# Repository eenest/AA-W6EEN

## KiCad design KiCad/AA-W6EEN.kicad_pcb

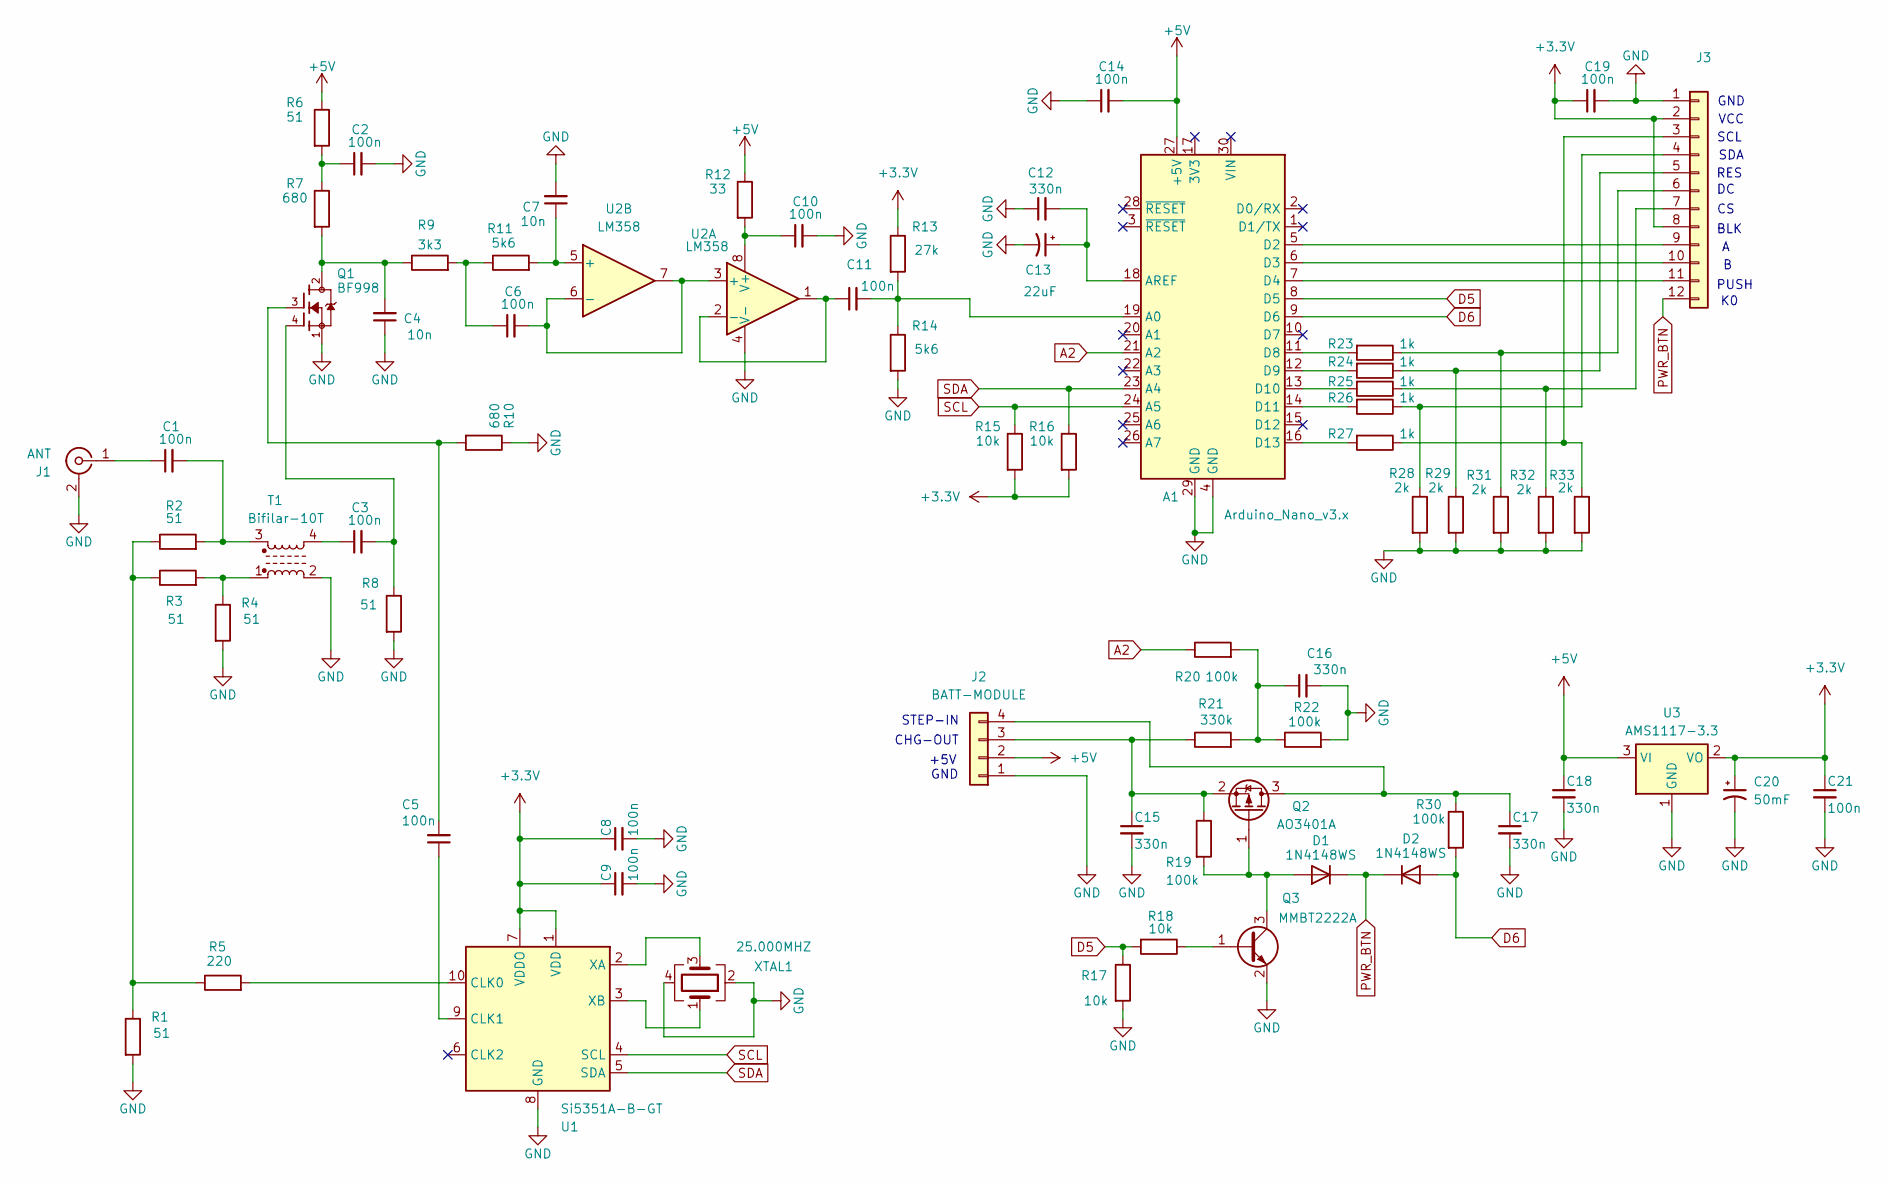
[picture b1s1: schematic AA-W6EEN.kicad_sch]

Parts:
A1: Arduino_Nano_v3.x; Arduino_Nano
C1, C2, C3, C5, C6, C8, C9, C10, C11, C14, C19, C21: 100n; C_0805_2012Metric_Pad1.18x1.45mm_HandSolder
C4, C7: 10n; C_0805_2012Metric_Pad1.18x1.45mm_HandSolder
C12, C15, C16, C17, C18: 330n; C_0805_2012Metric_Pad1.18x1.45mm_HandSolder
C13: 22uF; CP_Elec_4x3
C20: 50mF; C_Elec_6.3x7.7
D1, D2: 1N4148WS; D_SOD-123F
J1: ANT; BNC_Amphenol_B6252HB-NPP3G-50_Horizontal
J2: BATT-MODULE; JST_XH_B4B-XH-A_1x04_P2.50mm_Vertical
J3: 2.4" TFT with EC11; PinSocket_1x12_P2.54mm_Vertical
Q1: BF998; SOT190P230X110-4N
Q2: AO3401A; SOT-23
Q3: MMBT2222A; SOT-23
R1, R2, R3, R4, R6, R8: 51; R_0805_2012Metric_Pad1.20x1.40mm_HandSolder
R5: 220; R_0805_2012Metric_Pad1.20x1.40mm_HandSolder
R7, R10: 680; R_0805_2012Metric_Pad1.20x1.40mm_HandSolder
R9: 3k3; R_0805_2012Metric_Pad1.20x1.40mm_HandSolder
R11, R14: 5k6; R_0805_2012Metric_Pad1.20x1.40mm_HandSolder
R12: 33; R_0805_2012Metric_Pad1.20x1.40mm_HandSolder
R13: 27k; R_0805_2012Metric_Pad1.20x1.40mm_HandSolder
R15, R16, R17, R18: 10k; R_0805_2012Metric_Pad1.20x1.40mm_HandSolder
R19, R20, R22, R30: 100k; R_0805_2012Metric_Pad1.20x1.40mm_HandSolder
R21: 330k; R_0805_2012Metric_Pad1.20x1.40mm_HandSolder
R23, R24, R25, R26, R27: 1k; R_0805_2012Metric_Pad1.20x1.40mm_HandSolder
R28, R29, R31, R32, R33: 2k; R_0805_2012Metric_Pad1.20x1.40mm_HandSolder
T1: Bifilar-10T; Transformer_Toroid_Horizontal_D14.0mm_Amidon-T50
U1: Si5351A-B-GT; MSOP-10_3x3mm_P0.5mm
U2: LM358; My-SOIC8
U3: AMS1117-3.3; SOT-223-3_TabPin2
XTAL1: 25.000MHZ; Crystal_SMD_3225-4Pin_3.2x2.5mm

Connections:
+3.3V: C8.1, C9.1, C19.1, C20.1, C21.1, J3.2, J3.8, R13.1, R15.2, R16.2, U1.1 (VDD), U1.7 (VDDO), U3.2 (VO)
+5V: A1.27 (+5V), C14.2, C18.1, J2.2, R6.1, R12.1, U3.3 (VI)
A2: A1.21 (A2), R20.1
D5: A1.8 (D5), R17.1, R18.2
D6: A1.9 (D6), D2.2 (A), R30.2
GND: A1.4 (GND), A1.29 (GND), C2.2, C4.1, C7.2, C8.2, C9.2, C10.2, C12.1, C13.2, C14.1, C15.2, C16.2, C17.2, C18.2, C19.2, C20.2, C21.2, J1.2 (Ext), J2.1, J3.1, Q1.1, Q3.2 (E), R1.2, R4.2, R8.2, R10.1, R14.2, R17.2, R22.2, R28.2, R29.2, R31.2, R32.2, R33.2, T1.2, U1.8 (GND), U2.4 (V-), U3.1 (GND), XTAL1.2, XTAL1.4
unnamed: A1.19 (A0), C11.2, R13.2, R14.1
unnamed: A1.18 (AREF), C12.2, C13.1
unnamed: A1.5 (D2), J3.9
unnamed: A1.6 (D3), J3.10
unnamed: A1.7 (D4), J3.11
unnamed: A1.11 (D8), R23.2
unnamed: A1.12 (D9), R24.2
unnamed: A1.13 (D10), R25.2
unnamed: A1.14 (D11), R26.2
unnamed: A1.16 (D13), R27.2
unnamed: C1.2, R2.2, T1.3
unnamed: C2.1, R6.2, R7.1
unnamed: C3.1, T1.4
unnamed: C3.2, Q1.4, R8.1
unnamed: C4.2, Q1.2, R7.2, R9.1
unnamed: C5.2, Q1.3, R10.2
unnamed: C6.1, R9.2, R11.1
unnamed: C16.1, R20.2, R21.2, R22.1
unnamed: D1.2 (A), Q2.1 (G), Q3.3 (C), R19.2
unnamed: C1.1, J1.1 (In)
unnamed: C15.1, J2.3, Q2.2 (S), R19.1, R21.1
unnamed: C17.1, J2.4, Q2.3 (D), R30.1
unnamed: J3.3, R27.1, R33.1
unnamed: J3.4, R26.1, R28.1
unnamed: J3.5, R24.1, R29.1
unnamed: J3.6, R23.1, R31.1
unnamed: J3.7, R25.1, R32.1
unnamed: Q3.1 (B), R18.1
unnamed: R1.1, R2.1, R3.1, R5.1
unnamed: R3.2, R4.1, T1.1
unnamed: R5.2, U1.10 (CLK0)
unnamed: C5.1, U1.9 (CLK1)
unnamed: U1.2 (XA), XTAL1.3
unnamed: U1.3 (XB), XTAL1.1
unnamed: C6.2, U2.3 (+), U2.6 (-), U2.7
unnamed: C11.1, U2.1, U2.2 (-)
unnamed: C7.1, R11.2, U2.5 (+)
unnamed: C10.1, R12.2, U2.8 (V+)
PWR_BTN: D1.1 (K), D2.1 (K), J3.12
SCL: A1.24 (A5), R15.1, U1.4 (SCL)
SDA: A1.23 (A4), R16.1, U1.5 (SDA)

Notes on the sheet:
+5V
GND
STEP-IN
PUSH
SDA
CHG-OUT
BLK
VCC
RES
SCL

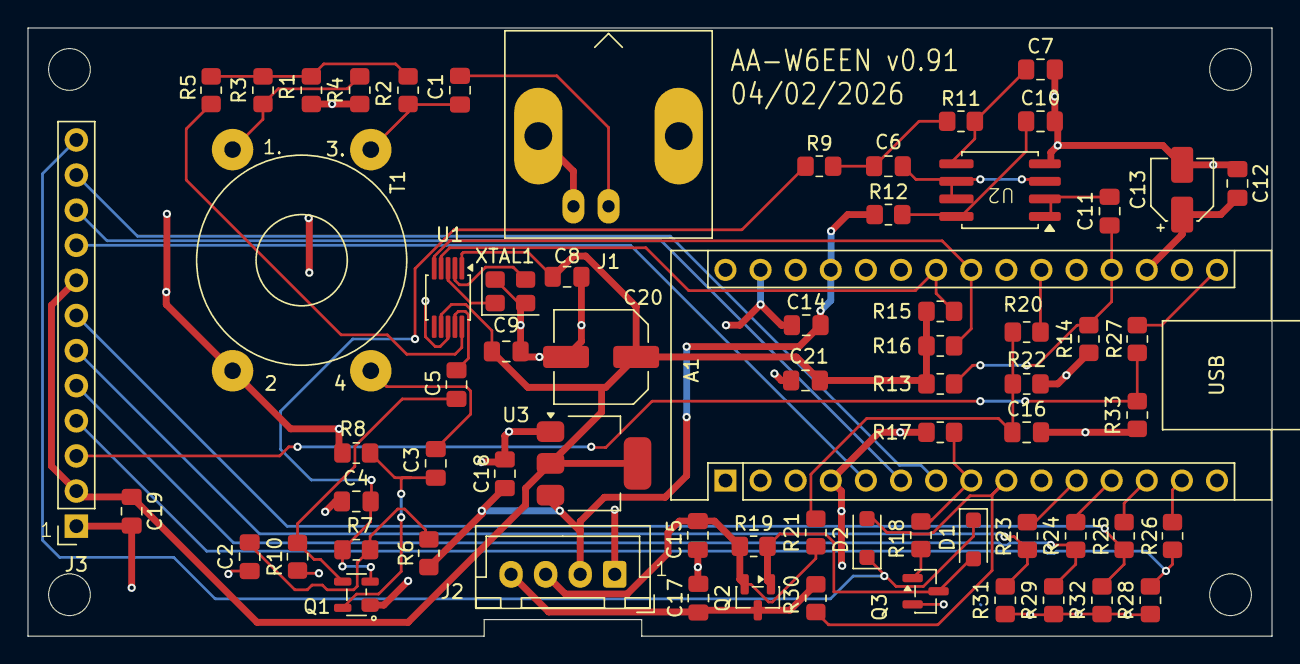
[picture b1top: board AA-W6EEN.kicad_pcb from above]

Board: 2 copper layers, 90.0 x 44.0 mm, 68 parts (0 on the bottom side), 47 nets.

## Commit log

2026-04-01 Initial save to GitHub
2026-04-02 Updated OPAMP footprint. Changed date/revision.
2026-04-02 Updated SOIC8 footprijt. Fixed pwr silkscreen labels. Changed revision/date
2026-04-02 General cleanup
